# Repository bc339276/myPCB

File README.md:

# myPCB
 20240319 kiCAD繪製電路與 PCB輸出入門

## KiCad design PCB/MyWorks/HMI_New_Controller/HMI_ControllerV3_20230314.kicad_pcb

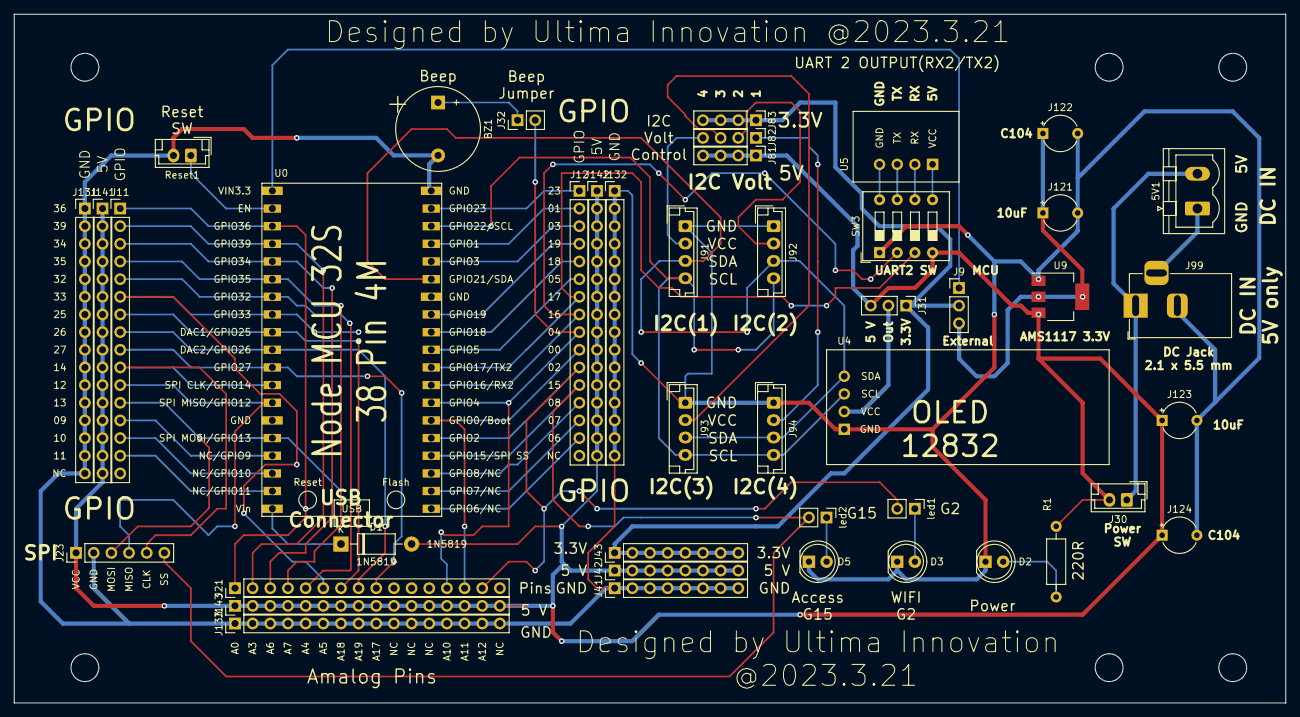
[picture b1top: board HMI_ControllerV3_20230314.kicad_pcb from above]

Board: 2 copper layers, 182.9 x 99.1 mm, 44 parts (0 on the bottom side), 54 nets.

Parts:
5V1: GND; PhoenixContact_MSTBVA_2,5_2-G_1x02_P5.00mm_Vertical
BZ1: Buzzer; Buzzer_12x9.5RM7.6
D1: 1N5819; D_DO-41_SOD81_P10.16mm_Horizontal
D2: Power Led; LED_D5.0mm_IRBlack
D3: Wifi Led(2); LED_D5.0mm_IRBlack
D5: Access Led(15); LED_D5.0mm_IRBlack
J9: 3.3V Internal/Exernam; PinHeader_1x03_P2.54mm_Vertical
J11: Left_GPIO; PinHeader_1x16_P2.54mm_Vertical
J12: Right_GPIO; PinHeader_1x16_P2.54mm_Vertical
J21: ADC; PinHeader_1x16_P2.54mm_Vertical
J23: SPI Connector; PinHeader_1x06_P2.54mm_Vertical
J30: Power SW; JST_EH_B2B-EH-A_1x02_P2.50mm_Vertical
J31: Oled Volt(3.3V/5V); PinHeader_1x03_P2.54mm_Vertical
J32: Jumper_2_For Buzzer; PinHeader_1x02_P2.54mm_Vertical
J41: Power GND; PinHeader_1x08_P2.54mm_Vertical
J42: Power 5V; PinHeader_1x08_P2.54mm_Vertical
J43: Power 3.3 V; PinHeader_1x08_P2.54mm_Vertical
J81: 5V; PinHeader_1x04_P2.54mm_Vertical
J82: Out; PinHeader_1x04_P2.54mm_Vertical
J83: 3.3V; PinHeader_1x04_P2.54mm_Vertical
J91: I2C(1); JST_EH_B4B-EH-A_1x04_P2.50mm_Vertical
J92: I2C(2); JST_EH_B4B-EH-A_1x04_P2.50mm_Vertical
J93: I2C(3); JST_EH_B4B-EH-A_1x04_P2.50mm_Vertical
J94: I2C(4); JST_EH_B4B-EH-A_1x04_P2.50mm_Vertical
J99: Barrel_Jack; BarrelJack_Horizontal
J121, J123: 10uF; CP_Radial_Tantal_D5.0mm_P5.00mm
J122, J124: C 104; CP_Radial_Tantal_D5.0mm_P5.00mm
J131: Right_GPIO_GND; PinHeader_1x16_P2.54mm_Vertical
J132: Left_GPIO_GND; PinHeader_1x16_P2.54mm_Vertical
J133: ADC_GND; PinHeader_1x16_P2.54mm_Vertical
J141: Right_GPIO_5V; PinHeader_1x16_P2.54mm_Vertical
J142: Leftt_GPIO_5V; PinHeader_1x16_P2.54mm_Vertical
J143: ADC_5V; PinHeader_1x16_P2.54mm_Vertical
R1: 220R; R_Axial_DIN0207_L6.3mm_D2.5mm_P10.16mm_Horizontal
Reset1: Jumper; JST_EH_B2B-EH-A_1x02_P2.50mm_Vertical
SW3: UART2 SW; SW_DIP_SPSTx04_Slide_9.78x12.34mm_W7.62mm_P2.54mm
U0: NodeMCU_32SV2; NodeMCU32SV2
U4: OLED12832_0.9
U5: USARTHMI
U9: AMS1117-3.3; SOT-223-3_TabPin2
led1: WIFI LED SW; PinHeader_1x02_P2.54mm_Vertical
led2: Access LED SW; PinHeader_1x02_P2.54mm_Vertical

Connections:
3.3V: J9.2, J31.1, J43.1, J43.2, J43.3, J43.4, J43.5, J43.6, J43.7, J43.8, J83.1, J83.2, J83.3, J83.4
5V: D1.2, J23.1, J30.2, J31.3, J42.1, J42.2, J42.3, J42.4, J42.5, J42.6, J42.7, J42.8, J81.1, J81.2, J81.3, J81.4, J123.1, J124.1, J141.1, J141.2, J141.3, J141.4, J141.5, J141.6, J141.7, J141.8, J141.9, J141.10, J141.11, J141.12, J141.13, J141.14, J141.15, J141.16, J142.1, J142.2, J142.3, J142.4, J142.5, J142.6, J142.7, J142.8, J142.9, J142.10, J142.11, J142.12, J142.13, J142.14, J142.15, J142.16, J143.1, J143.2, J143.3, J143.4, J143.5, J143.6, J143.7, J143.8, J143.9, J143.10, J143.11, J143.12, J143.13, J143.14, J143.15, J143.16, R1.1, SW3.4, U9.3
EX3.3V: J9.3, J121.1, J122.1, U9.2
EXGND: SW3.8, U5.4
EX_RX: SW3.7, U5.3
EX_TX: SW3.6, U5.2
EX_V: SW3.5, U5.1
GND: BZ1.2, D2.1, D3.1, D5.1, J23.2, J41.1, J41.2, J41.3, J41.4, J41.5, J41.6, J41.7, J41.8, J91.1, J92.1, J93.1, J94.1, J99.2, J121.2, J122.2, J123.2, J124.2, J131.1, J131.2, J131.3, J131.4, J131.5, J131.6, J131.7, J131.8, J131.9, J131.10, J131.11, J131.12, J131.13, J131.14, J131.15, J131.16, J132.1, J132.2, J132.3, J132.4, J132.5, J132.6, J132.7, J132.8, J132.9, J132.10, J132.11, J132.12, J132.13, J132.14, J132.15, J132.16, J133.1, J133.2, J133.3, J133.4, J133.5, J133.6, J133.7, J133.8, J133.9, J133.10, J133.11, J133.12, J133.13, J133.14, J133.15, J133.16, Reset1.2, SW3.1, U0.38, U4.1, U9.1
GPIO0: J12.10, J21.14, U0.25
GPIO1: J12.2, U0.35
GPIO2: J12.11, J21.15, U0.24, led1.2
GPIO3: J12.3, U0.34
GPIO4: J12.9, J21.13, J32.2, U0.26
GPIO5: J12.6, U0.29
GPIO6: J12.15, U0.20
GPIO7: J12.14, U0.21
GPIO8: J12.13, U0.22
GPIO9: J11.13, U0.16
GPIO10: J11.14, U0.17
GPIO11: J11.15, U0.18
GPIO12: J11.11, J23.4, U0.13
GPIO13: J11.12, J23.3, U0.15
GPIO14: J11.10, J23.5, U0.12
GPIO15: J12.12, J23.6, U0.23, led2.2
GPIO16: J12.8, SW3.2, U0.27
GPIO17: J12.7, SW3.3, U0.28
GPIO18: J12.5, U0.30
GPIO19: J12.4, U0.31
GPIO23: J12.1, U0.37
GPIO25: J11.7, J21.7, U0.9
GPIO26: J11.8, J21.8, U0.10
GPIO27: J11.9, J21.9, U0.11
GPIO32: J11.5, J21.5, U0.7
GPIO33: J11.6, J21.6, U0.8
GPIO34: J11.3, J21.3, U0.5
GPIO35: J11.4, J21.4, U0.6
GPIO36: J11.1, J21.1, U0.3
GPIO39: J11.2, J21.2, U0.4
I2CVCC1: J82.4, J91.2
I2CVCC2: J82.2, J92.2
I2CVCC3: J82.3, J93.2
I2CVCC4: J82.1, J94.2
MCU3.3: J9.1, U0.1
unnamed: 5V1.1, J99.3
unnamed: 5V1.2, J30.1, J99.1
unnamed: BZ1.1, J32.1
unnamed: D2.2, R1.2
unnamed: D3.2, led1.1
unnamed: D5.2, led2.1
OLEDVCC: J31.2, U4.2
RESET: Reset1.1, U0.2
SCL: J91.4, J92.4, J93.4, J94.4, U0.36, U4.3
SDA: J91.3, J92.3, J93.3, J94.3, U0.33, U4.4
VIN: D1.1, U0.19

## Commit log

2024-03-19 commit all
